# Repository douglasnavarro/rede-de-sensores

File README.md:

# rede-de-sensores
Rede de sensores de presença

Confira uma apresentação em [vídeo do projeto](https://www.youtube.com/watch?v=fuPidej-O7c&t=0s&list=PLMp4nLC2kXhuEHrjNnDw4fBF1sRVGfNI7&index=10).

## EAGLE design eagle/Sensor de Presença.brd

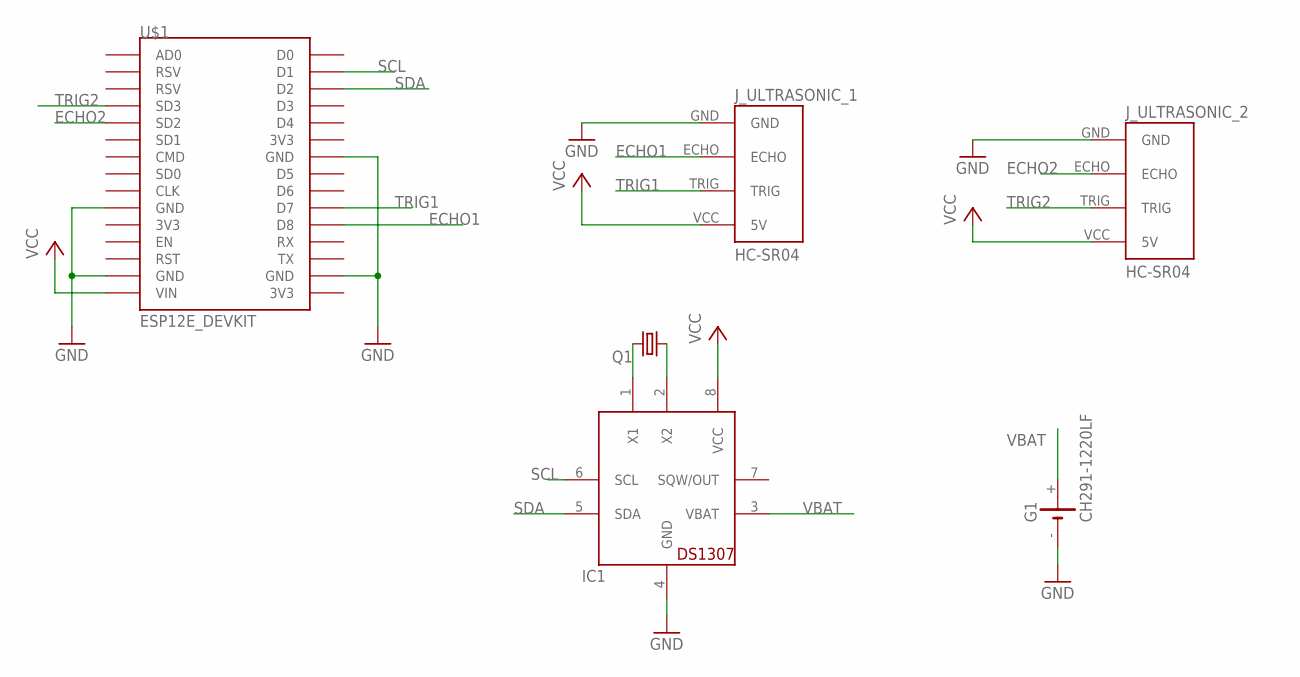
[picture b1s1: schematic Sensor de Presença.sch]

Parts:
G1: CH291-1220LF
IC1: DS1307; DIL08
J_ULTRASONIC_1, J_ULTRASONIC_2: HC-SR04; HC-SR04_FOOTPRINT
Q1: CRYSTALTC38H; TC38H
U$1: ESP12E_DEVKIT

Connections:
ECHO1: J_ULTRASONIC_1.ECHO, U$1.D8
ECHO2: J_ULTRASONIC_2.ECHO, U$1.SD2
GND: G1.-, IC1.4 (GND), J_ULTRASONIC_1.GND, J_ULTRASONIC_2.GND, U$1.GND@0 (GND), U$1.GND@1 (GND), U$1.GND@2 (GND), U$1.GND@3 (GND)
unnamed: IC1.1 (X1), Q1.2
unnamed: IC1.2 (X2), Q1.1
SCL: IC1.6 (SCL), U$1.D1
SDA: IC1.5 (SDA), U$1.D2
TRIG1: J_ULTRASONIC_1.TRIG, U$1.D7
TRIG2: J_ULTRASONIC_2.TRIG, U$1.SD3
VBAT: G1.+, IC1.3 (VBAT)
VCC: IC1.8 (VCC), J_ULTRASONIC_1.VCC (5V), J_ULTRASONIC_2.VCC (5V), U$1.VIN

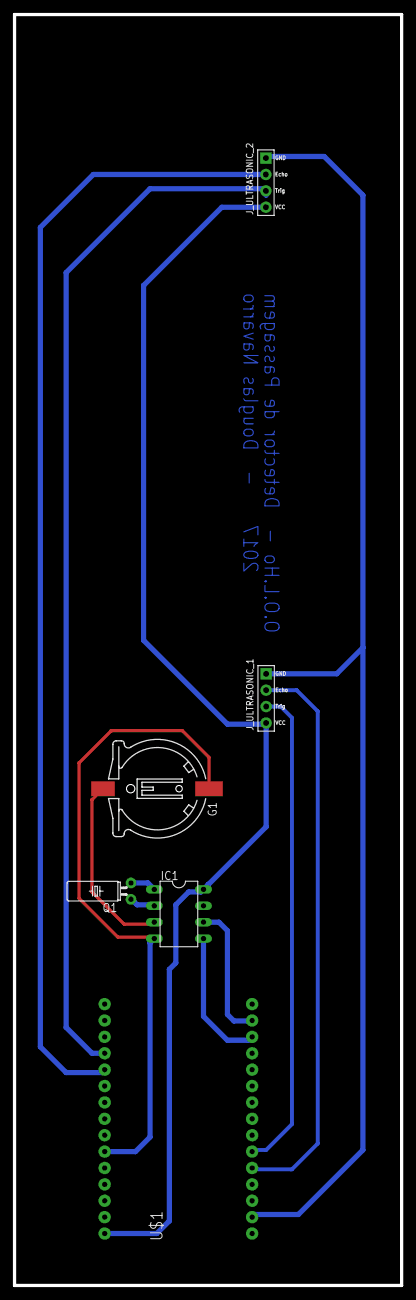
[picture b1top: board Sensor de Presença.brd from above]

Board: 2 copper layers, 60.0 x 197.0 mm, 6 parts (0 on the bottom side), 11 nets.

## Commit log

2017-07-07 fixed name
2017-07-07 minor adjustments
2017-09-02 added eagle .sch rev 1.0
2017-10-01 first version passage detector
2017-10-29 add http_client.ino
2017-11-05 presence detection working fairly well
2017-11-05 continuously scanning and making requests. no RTC
2017-11-07 new server hostname
2017-11-18 added full functionality with RTC
2017-11-18 add full functionality with RTC
2017-11-25 updated eagle project to include 2 ultrassonic sensors and ds1307 rtc
2017-12-17 added final prototype pcb layout and text

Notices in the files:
parts and their libraries:
SparkFun-Aesthetics: Licensing: Creative Commons ShareAlike 4.0 International - https://creativecommons.org/licenses/by-sa/4.0
